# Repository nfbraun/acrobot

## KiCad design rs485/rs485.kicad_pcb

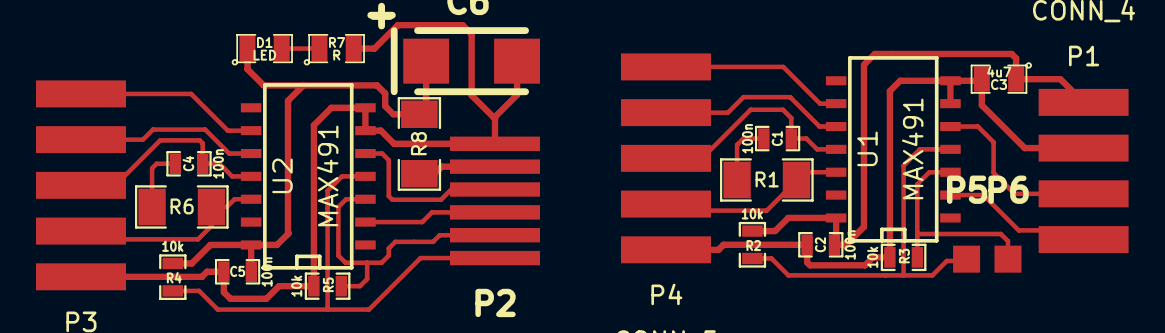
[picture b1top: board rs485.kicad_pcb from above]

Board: 2 copper layers, 23 parts (0 on the bottom side), 21 nets.

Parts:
C1, C2, C4, C5: 100n; SMD-0603_c
C3: 4u7; SMD-0805
C6: 15u; TantalC_SizeC_EIA-6032_Reflow
D1: LED; SMD-0805
P1: CONN_4; CONN_0.1inch_4x_5x1.5mm
P2: CONN_6; FLATCONN_6
P3, P4: CONN_5; CONN_0.1inch_5x_1.5x5mm
P5, P6: CONN_1; Measurement_Point_Square-SMD-Pad_Small
R1, R6: 120; SMD-1206
R2, R3, R4, R5: 10k; SMD-0603_r
R7: R; SMD-0805
R8: 0; SMD-1206
U1, U2: MAX491; SOIC-14_N

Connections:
+5V: C2.1, C3.1, C5.1, C6.1, D1.1, P1.4, P2.2, R2.1, R4.1, R8.1, R8.2, U1.14, U2.14
GND: C2.2, C3.2, C5.2, C6.2, P1.3, P2.1, P3.5, P4.5, R3.1, R5.1, R7.2, U1.6, U1.7, U2.6, U2.7
unnamed: C1.1, R1.1
unnamed: C1.2, P4.3, U1.11
unnamed: C4.1, P3.3, U2.11
unnamed: C4.2, R6.1
unnamed: D1.2, R7.1
unnamed: P1.1, U1.2
unnamed: P1.2, U1.5
unnamed: P2.3, U2.5
unnamed: P2.4, U2.2
unnamed: P2.5, R5.2, U2.3
unnamed: P2.6, R4.2, U2.4
unnamed: P3.1, U2.9
unnamed: P3.2, U2.10
unnamed: P3.4, R6.2, U2.12
unnamed: P4.1, U1.9
unnamed: P4.2, U1.10
unnamed: P4.4, R1.2, U1.12
unnamed: P5.1, R2.2, U1.4
unnamed: P6.1, R3.2, U1.3

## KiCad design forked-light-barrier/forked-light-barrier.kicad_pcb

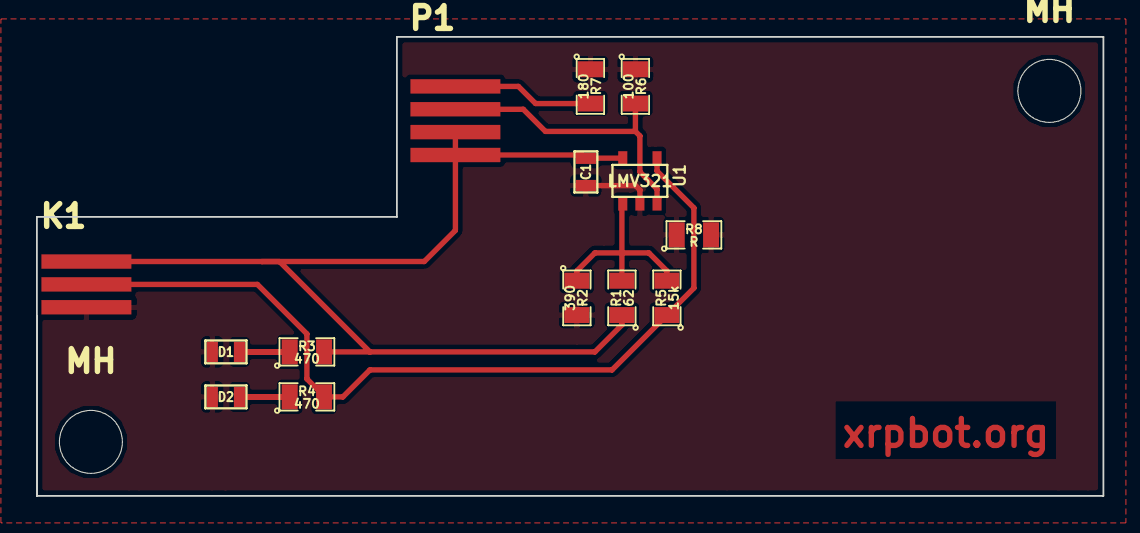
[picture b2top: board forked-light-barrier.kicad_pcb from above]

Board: 2 copper layers, 59.2 x 25.5 mm, 16 parts (0 on the bottom side), 8 nets.

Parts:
C1: C; SM0603
D1, D2: LED; SM0603
K1: CONN_3; FLATCONN_3
MH: MountingHole_3-5mm_RevA_Date21Jun2010; MountingHole_3-5mm
MH#2: MountingHole_3-5mm_RevA_Date21Jun2010; MountingHole_3-5mm
P1: CONN_4; FLATCONN_4
R1: 62; SM0805
R2: 390; SM0805
R3, R4: 470; SM0805
R5: 15k; SM0805
R6: 100; SM0805
R7: 180; SM0805
R8: R; SM0805
U1: LMV321; SOT23-5

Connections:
5V: C1.1, K1.3, P1.1, P1.2, R1.1, R3.2, U1.5
/Emitter-: P1.4, R7.2
Detector-: P1.3, R6.2, U1.3
GND: C1.2, D1.2, D2.2, K1.1, R2.2, R6.1, R7.1, R8.1, R8.2, U1.2
unnamed: D1.1, R3.1
unnamed: D2.1, R4.1
unnamed: R1.2, R2.1, R5.2, U1.1
OUT: K1.2, R4.2, R5.1, U1.4

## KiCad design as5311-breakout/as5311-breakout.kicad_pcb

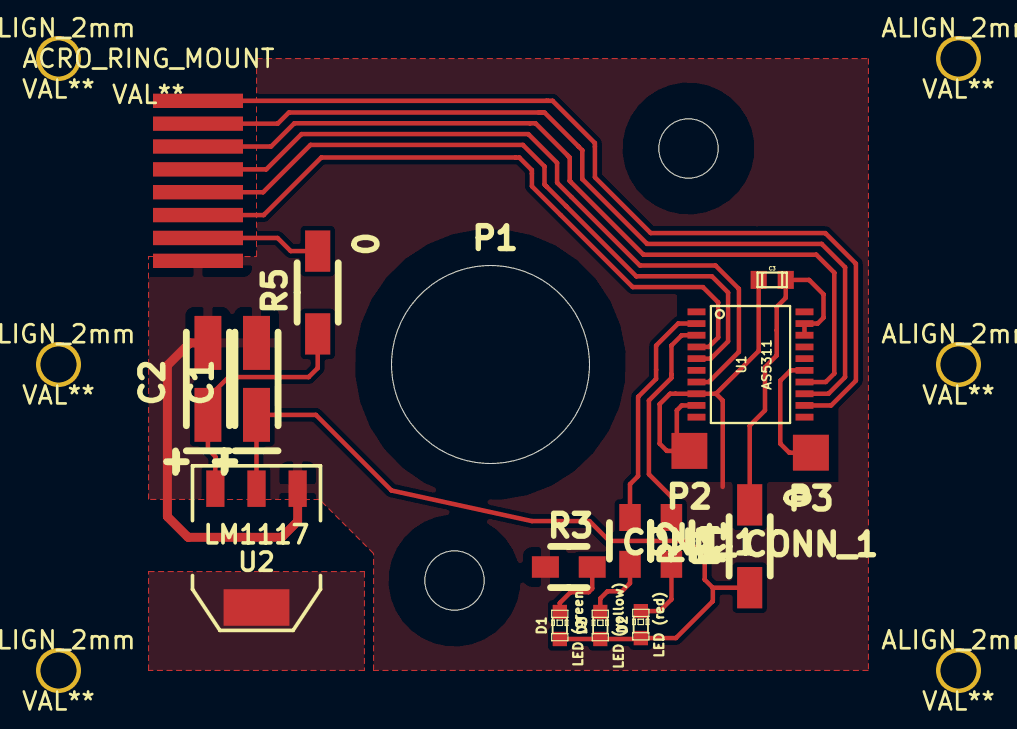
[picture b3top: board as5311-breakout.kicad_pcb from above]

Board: 2 copper layers, 23 parts (0 on the bottom side), 15 nets.

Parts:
ACRO_RING_MOUNT: VAL**; ACRO_RING_MOUNT
ALIGN_2mm, ALIGN_2mm#2, ALIGN_2mm#3, ALIGN_2mm#4, ALIGN_2mm#5, ALIGN_2mm#6: VAL**; ALIGN_2mm
C1, C2: 10µ; TantalC_SizeA_EIA-3216_HandSoldering
C3: 100n; c_0603
D1: LED (green); LED-0603
D2: LED (red); LED-0603
D3: LED (yellow); LED-0603
P1: CONN_8; FLATCONN_8
P2, P3: CONN_1; SQUARE_2x2
R1, R2, R3: R; Resistor_SMD0805_HandSoldering
R4, R5: 0; Resistor_SMD1206_HandSoldering
U1: AS5311; TSSOP-20_AS5311
U2: LM1117; SOT223

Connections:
A: P1.3, U1.4
B: P1.4, U1.5
CLK: P1.7, U1.13
CSn: P1.6, U1.14
DO: P1.8, U1.12
GND: C1.2, C2.2, C3.2, P1.1, P2.1, R3.1, U1.8, U1.9, U2.1
Idx: P1.5, U1.7
unnamed: D1.2, R3.2
unnamed: D2.2, R1.2
unnamed: D3.2, R2.2
unnamed: P3.1, U1.15
unnamed: R1.1, U1.3
unnamed: R2.1, U1.2
V_33: C1.1, C3.1, D1.1, D2.1, D3.1, R4.1, R4.2, U1.18, U1.19, U2.2, U2.4
V_50: C2.1, P1.2, R5.1, R5.2, U2.3

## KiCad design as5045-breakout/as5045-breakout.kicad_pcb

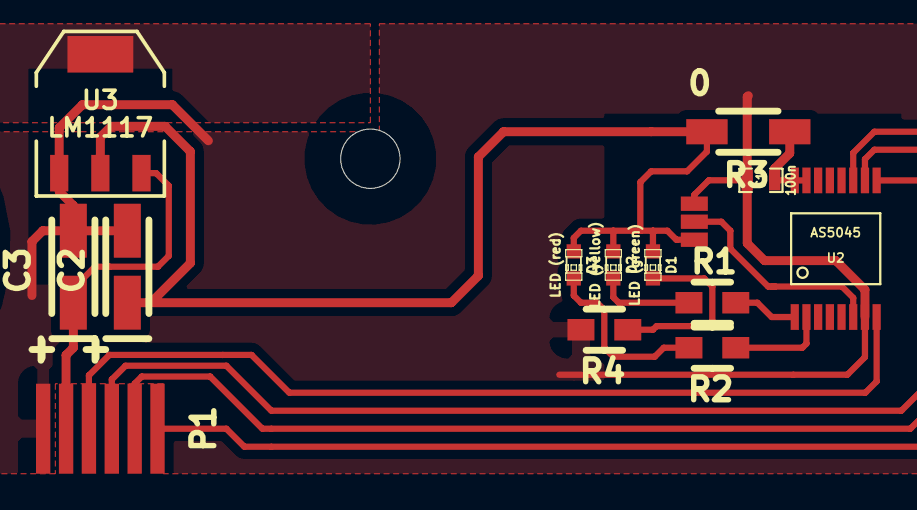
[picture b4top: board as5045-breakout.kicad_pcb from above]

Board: 2 copper layers, 15 parts (0 on the bottom side), 13 nets.

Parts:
ACRO_MOTOR_MOUNT: VAL**; ACRO_MOTOR_MOUNT
C1: 100n; SM0603_Capa
C2, C3: 10µ; TantalC_SizeA_EIA-3216_HandSoldering
D1: LED (green); LED-0603
D2: LED (yellow); LED-0603
D3: LED (red); LED-0603
P1: CONN_6; FLATCONN_6
R1, R2: 680R; Resistor_SMD0805_HandSoldering
R3: 0; Resistor_SMD1206_HandSoldering
R4: 680; Resistor_SMD0805_HandSoldering
U1: JMP_3; SOLDERSW_3
U2: AS5045; SSOP-16_AS5045
U3: LM1117; SOT223

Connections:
CLK: P1.5, U2.10
CSn: P1.6, U2.11
DO: P1.4, U2.9
GND: C1.2, C2.2, C3.2, P1.1, R4.2, U1.3, U2.7, U3.1
unnamed: D1.2, R4.1
unnamed: D2.2, R1.1
unnamed: D3.2, R2.2
unnamed: R1.2, U2.1
unnamed: R2.1, U2.2
unnamed: U1.2, U2.6
PROG: P1.3, U2.8
VCC: C1.1, C2.1, D1.1, D2.1, D3.1, R3.1, R3.2, U1.1, U2.15, U2.16, U3.2
V_IN: C3.1, P1.2, U3.3

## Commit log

2014-01-11 initial version (work in progress)
2014-01-22 work on BLDC power stage, begin board layout
2014-01-22 add HMC5883 breakout board
2014-02-10 begin work on active clamp board layout
2014-02-27 change kicad-modules to acrobot branch
2014-02-27 add daughter board for Hobbyking BLDC driver
2014-02-27 revert incorrectly moved file in commit eaefdc3a..
2014-02-27 add PSU protect board (late commit)
2014-06-09 add first working version of as5045 breakout
2014-06-09 update kicad modules
2014-06-19 work on AS5045 breakout
2014-06-19 add AS5311 (ring sensor) breakout
2014-06-19 add fork light barrier pcb
2014-10-14 add RS485 - RS232TTL converter board
2014-10-14 update kicad-modules
